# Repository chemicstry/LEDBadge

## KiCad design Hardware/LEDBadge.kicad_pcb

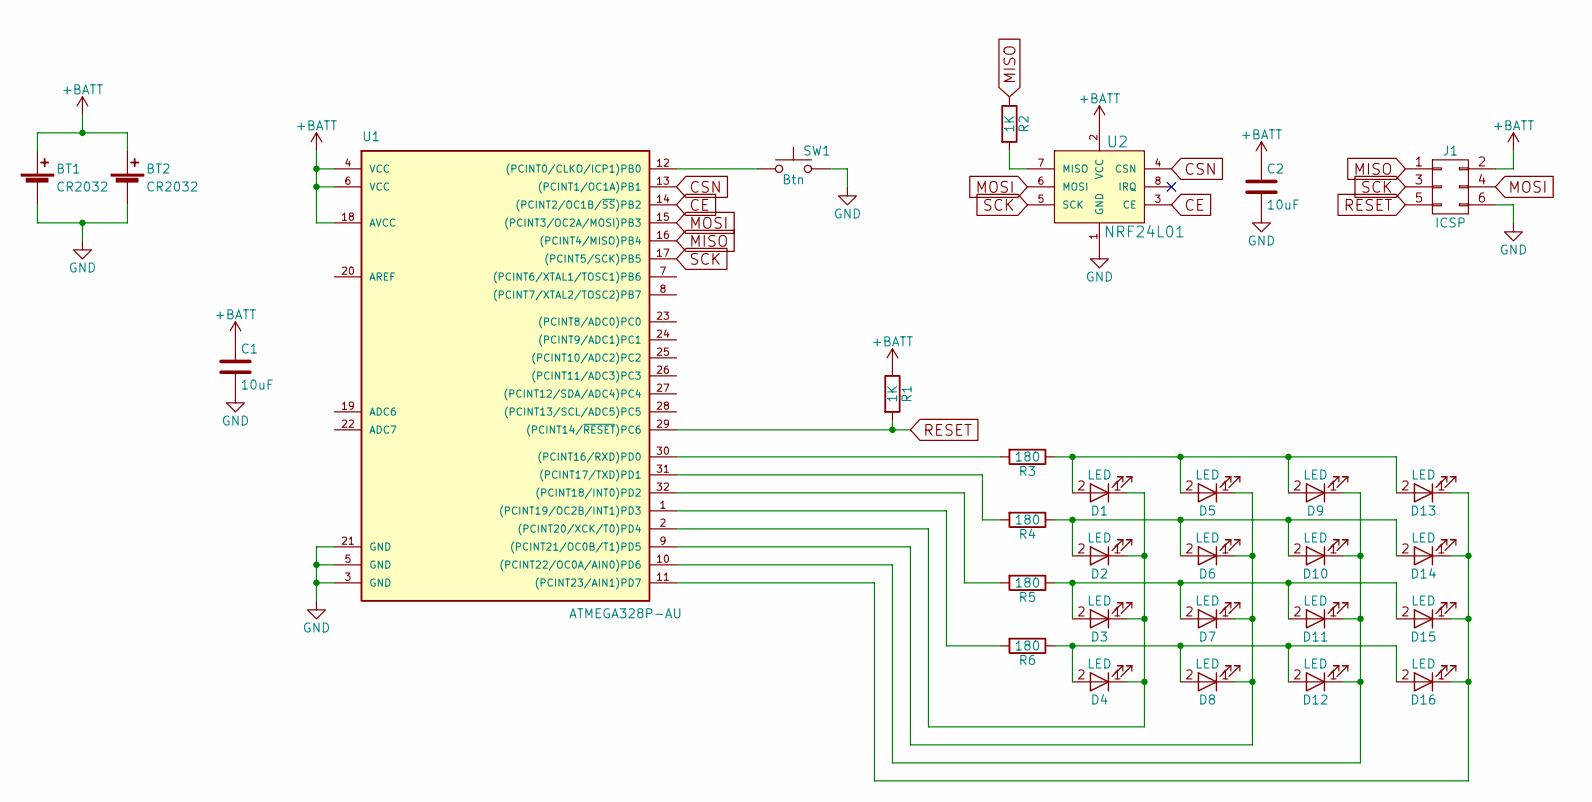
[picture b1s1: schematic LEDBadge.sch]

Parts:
BT1, BT2: CR2032; CCR-2008
C1, C2: 10uF; C_0805
D1, D2, D3, D4, D5, D6, D7, D8, D9, D10, D11, D12, D13, D14, D15, D16: LED; LED_0603
J1: ICSP; Pin_Header_Straight_2x03_Pitch2.54mm
R1, R2: 1K; R_0603
R3, R4, R5, R6: 180; R_0603
SW1: Btn; SW_SPST_SKQG
U1: ATMEGA328P-AU; TQFP-32_7x7mm_Pitch0.8mm
U2: NRF24L01; NRF24L01-SMD

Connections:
+BATT: BT1.1 (+), BT2.1 (+), C1.1, C2.1, J1.2, R1.1, U1.4 (VCC), U1.6 (VCC), U1.18 (AVCC), U2.2 (VCC)
CE: U1.14 ((PCINT2/OC1B/~SS~)PB2), U2.3 (CE)
CSN: U1.13 ((PCINT1/OC1A)PB1), U2.4 (CSN)
GND: BT1.2 (-), BT2.2 (-), C1.2, C2.2, J1.6, SW1.2, U1.3 (GND), U1.5 (GND), U1.21 (GND), U2.1 (GND)
MISO: J1.1, R2.1, U1.16 ((PCINT4/MISO)PB4)
MOSI: J1.4, U1.15 ((PCINT3/OC2A/MOSI)PB3), U2.6 (MOSI)
unnamed: D1.1 (K), D2.1 (K), D3.1 (K), D4.1 (K), U1.2 ((PCINT20/XCK/T0)PD4)
unnamed: D1.2 (A), D5.2 (A), D9.2 (A), D13.2 (A), R3.1
unnamed: D5.1 (K), D6.1 (K), D7.1 (K), D8.1 (K), U1.9 ((PCINT21/OC0B/T1)PD5)
unnamed: D9.1 (K), D10.1 (K), D11.1 (K), D12.1 (K), U1.10 ((PCINT22/OC0A/AIN0)PD6)
unnamed: D2.2 (A), D6.2 (A), D10.2 (A), D14.2 (A), R4.1
unnamed: D3.2 (A), D7.2 (A), D11.2 (A), D15.2 (A), R5.1
unnamed: D4.2 (A), D8.2 (A), D12.2 (A), D16.2 (A), R6.1
unnamed: D13.1 (K), D14.1 (K), D15.1 (K), D16.1 (K), U1.11 ((PCINT23/AIN1)PD7)
unnamed: R2.2, U2.7 (MISO)
unnamed: R3.2, U1.30 ((PCINT16/RXD)PD0)
unnamed: R4.2, U1.31 ((PCINT17/TXD)PD1)
unnamed: R5.2, U1.32 ((PCINT18/INT0)PD2)
unnamed: R6.2, U1.1 ((PCINT19/OC2B/INT1)PD3)
unnamed: SW1.1, U1.12 ((PCINT0/CLKO/ICP1)PB0)
RESET: J1.5, R1.2, U1.29 ((PCINT14/~RESET~)PC6)
SCK: J1.3, U1.17 ((PCINT5/SCK)PB5), U2.5 (SCK)

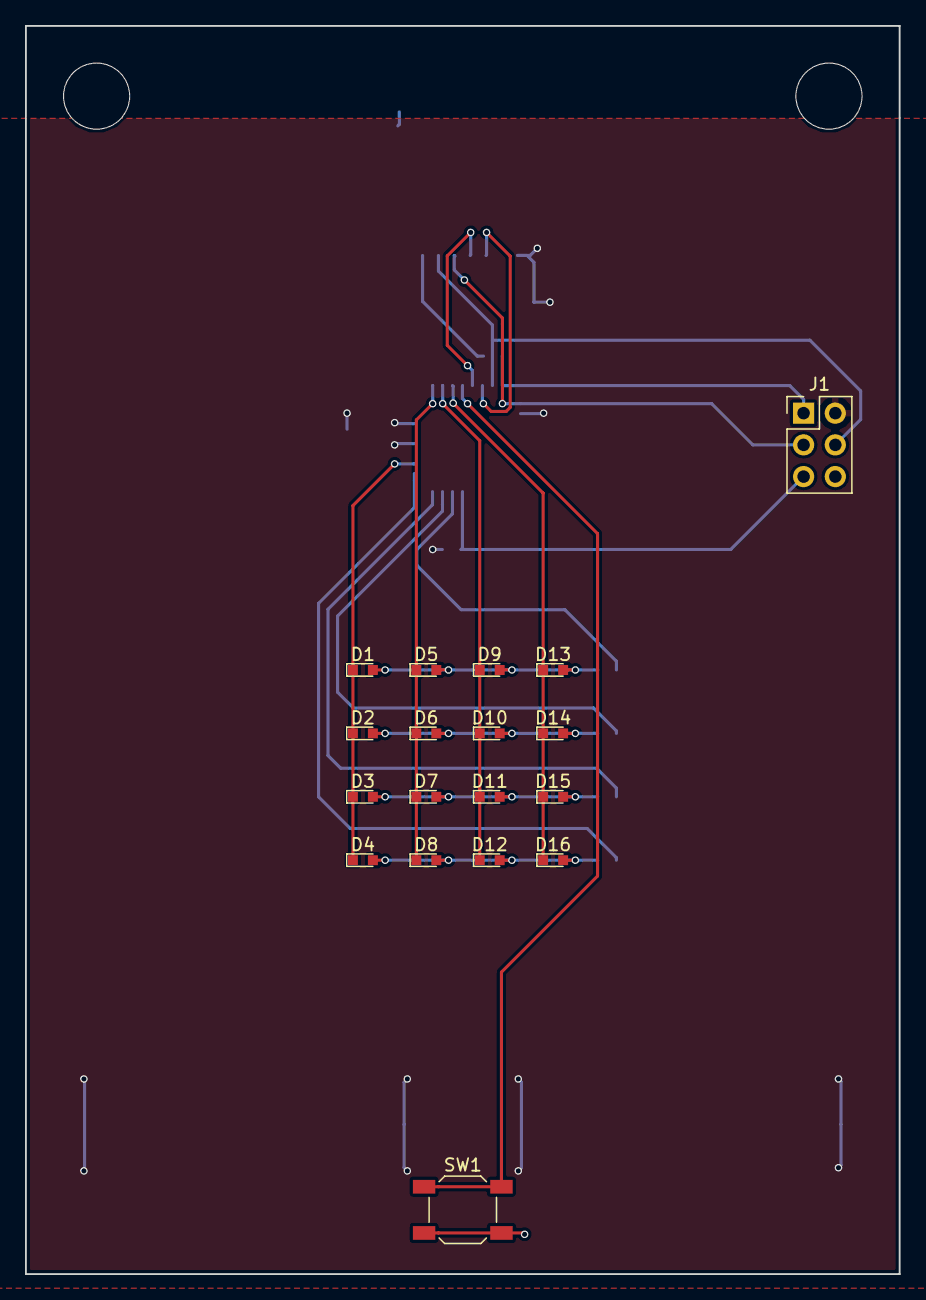
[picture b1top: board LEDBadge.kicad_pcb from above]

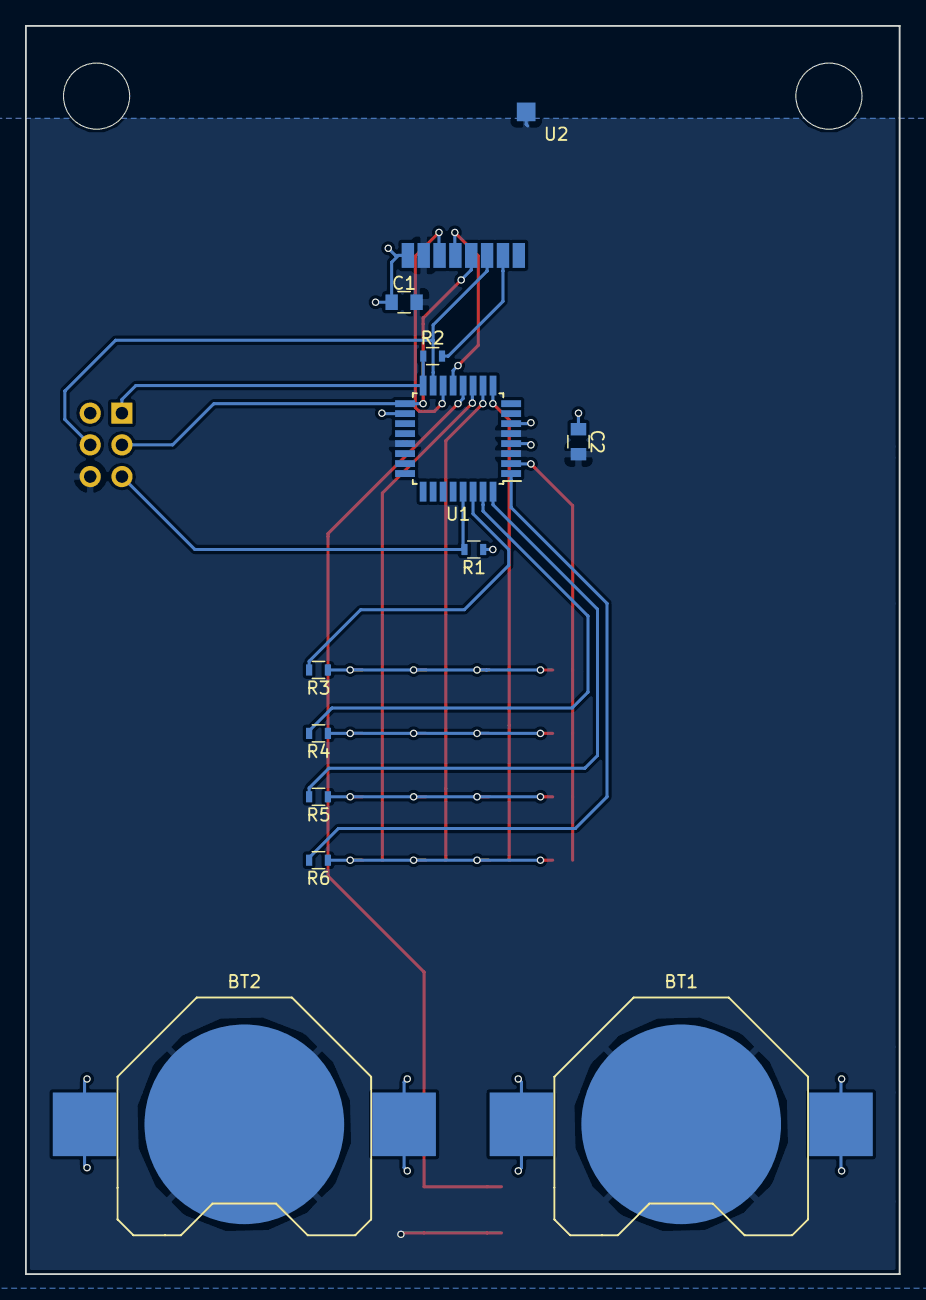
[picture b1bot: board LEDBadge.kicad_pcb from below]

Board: 2 copper layers, 70.0 x 100.0 mm, 30 parts (12 on the bottom side), 22 nets.

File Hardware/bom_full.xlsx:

part | url | price (EUR) | qty | total |  | Total: | 5.3100000000000005
atmega328 |  | 1 | 1 | 1
NRF24L01 |  | 0.75 | 1 | 0.75
CR2032 socket | https://www.aliexpress.com/item/10PCS-LOT-Battery-Button-Cel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 | 0.14000000000000001 | 1 | 0.14000000000000001
CR2032 battery |  | 1 | 1 | 1
PCB + PCBA |  | 2 | 1 | 2
LED | http://www.tme.eu/en/details/osg80603c1e/smd-colour-leds/opt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 | 0.02 | 16 | 0.32
Small stuff |  | 0.1 | 1 | 0.1

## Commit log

2017-09-08 First push
2017-09-11 Update PCB
2017-10-03 Transmitter code
